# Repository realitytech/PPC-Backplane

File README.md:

# PPC-Backplane
Amstrad PPC640 and PPC512 Internal PC104 Backplane

This adds an internal PC104 compatible slot to the PPC640 and PPC512 in the modem bay.
The board is designed to fit inside the machine soldering on the underside of the main board but can be fitted with through hole sockets and used externally too for testing and development.

This is the inital release version and corrects a few issues with the very first issue. The schematic and PCB need tidying.

NOTE: This version is UNTESTED and has not been built yet. It *should* work as it's an evolution of a design that DOES work. However it's missing changes that the test board has, notably.
Pullups on A8-A16, these seem to be not needed on all units.
Pullups on D0-D7 are optional, both units I have here already have these on the board.

The plan is to move to 74xxx16245 chips to keep to two chips but buffer ALL lines.

Licence/Useage:
Please credit the source. This is a non-commercial project and you may do with it as you wish for PERSONAL USE ONLY
Commercial use is strictly forbidden.

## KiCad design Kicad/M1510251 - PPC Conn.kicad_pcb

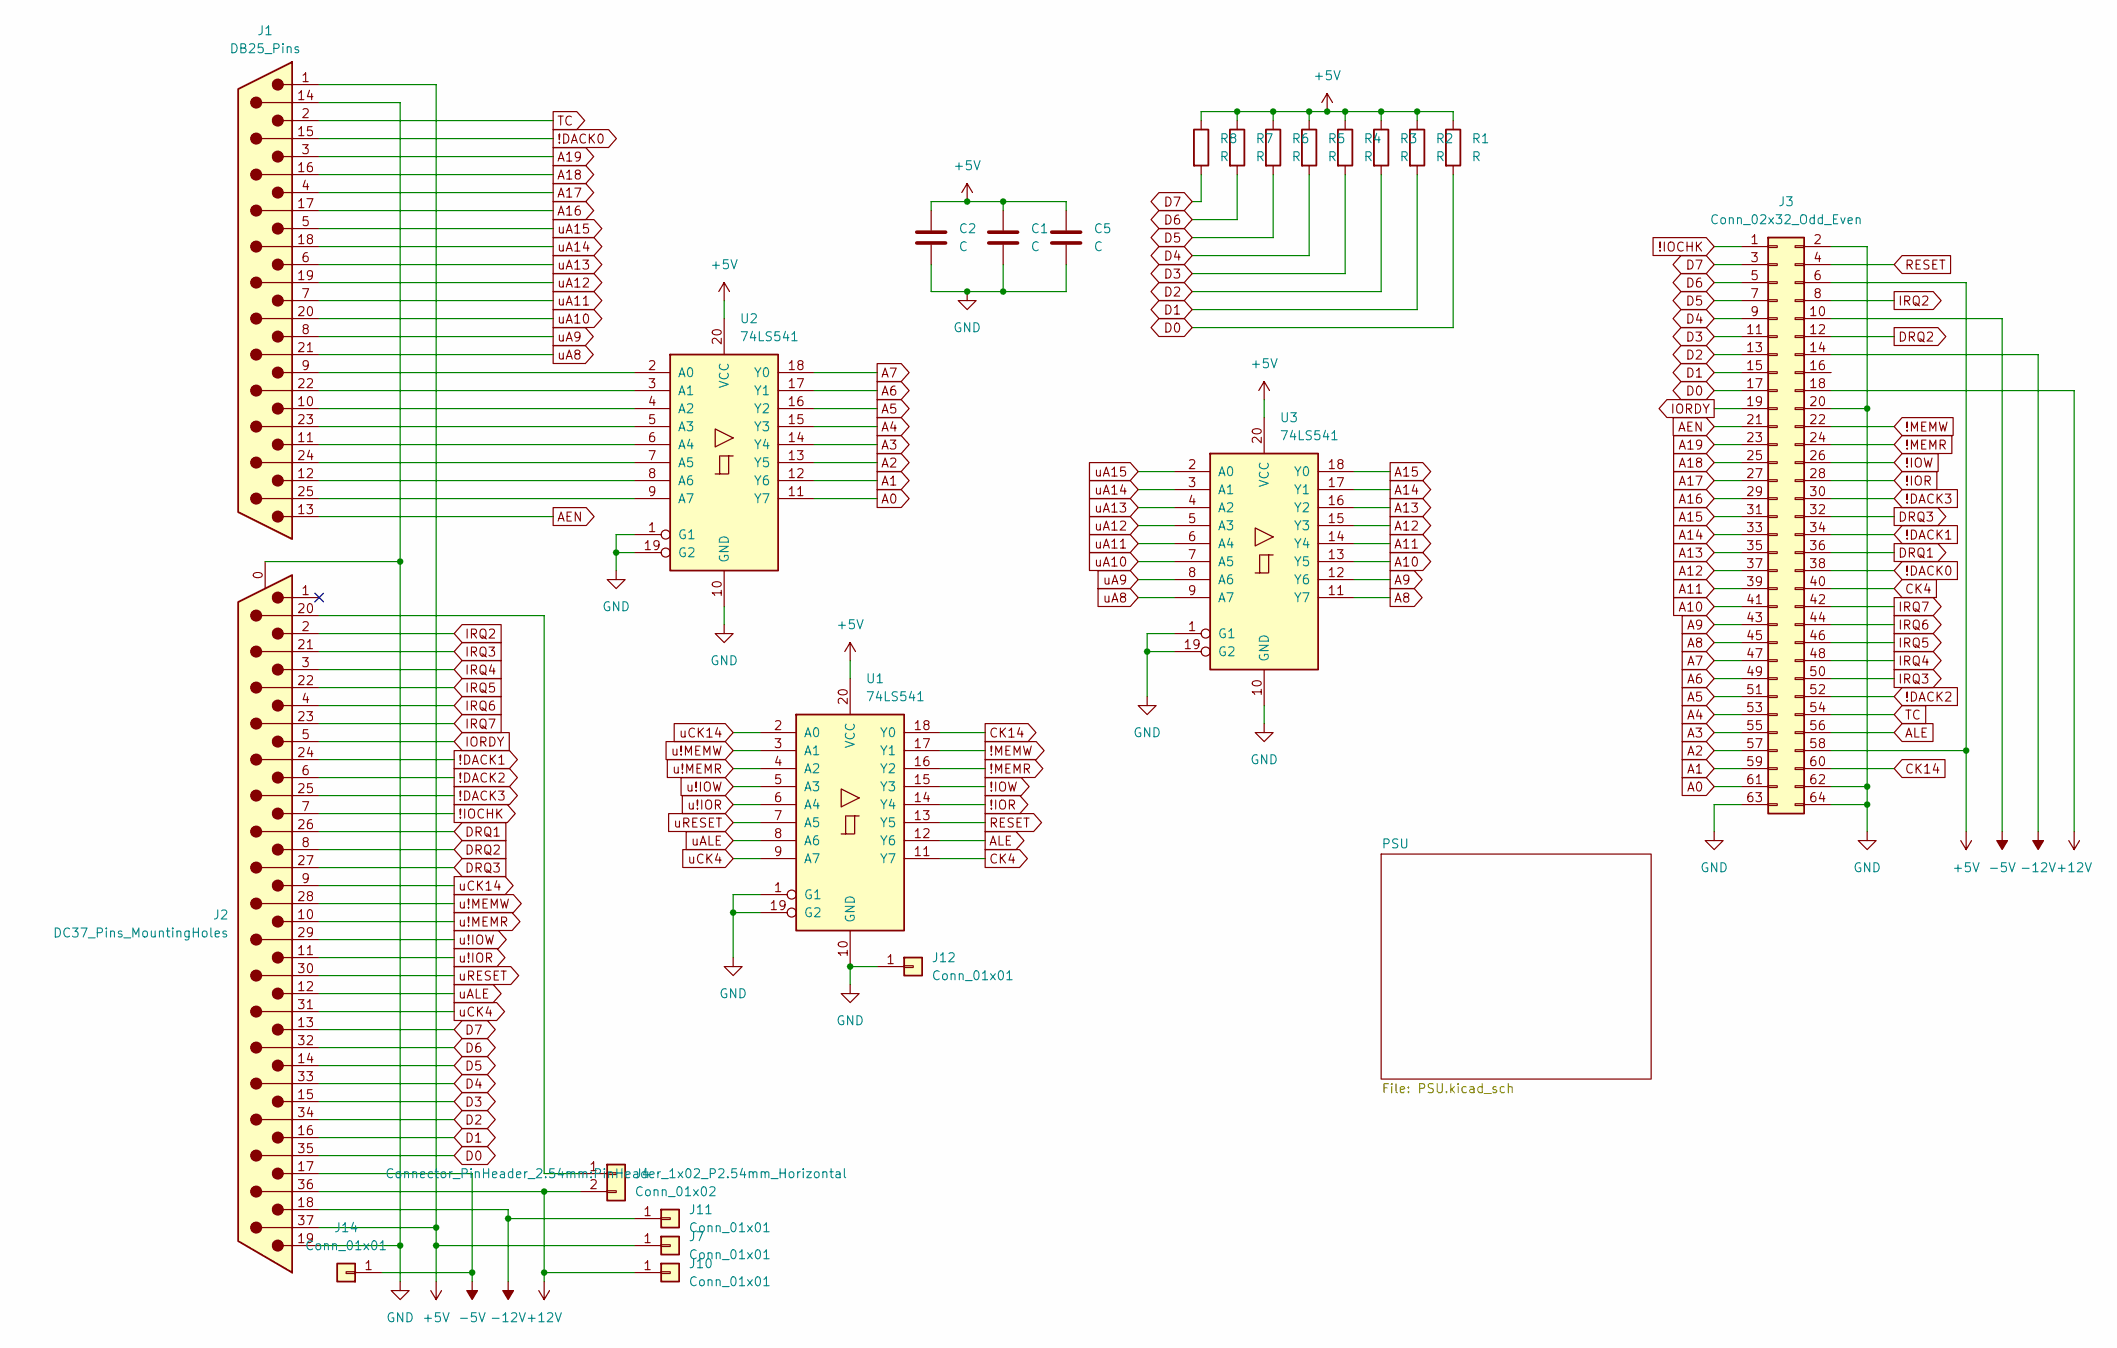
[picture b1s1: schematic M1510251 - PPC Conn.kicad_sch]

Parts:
C1, C2, C5: C; C_0805_2012Metric
J1: DB25_Pins; DSUB-25_Pins_Vertical_P2.77x2.84mm_MountingHoles
J2: DC37_Pins_MountingHoles; DSUB-37_Pins_Vertical_P2.77x2.84mm_MountingHoles
J3: Conn_02x32_Odd_Even; PinHeader_2x32_P2.54mm_Vertical
J4: Conn_01x02; PinHeader_1x02_P2.54mm_Horizontal
J7, J10, J11, J12, J14: Conn_01x01; SolderWire-0.15sqmm_1x01_D0.5mm_OD1.5mm
R1, R2, R3, R4, R5, R6, R7, R8: R; R_0805_2012Metric
U1, U2, U3: 74LS541; SSOP-20_4.4x6.5mm_P0.65mm

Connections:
!DACK0: J1.15, J3.38
!DACK1: J2.24, J3.34
!DACK2: J2.6, J3.52
!DACK3: J2.25, J3.30
!IOCHK: J2.7, J3.1
!IOR: J3.28, U1.14 (Y4)
!IOW: J3.26, U1.15 (Y3)
!MEMR: J3.24, U1.16 (Y2)
!MEMW: J3.22, U1.17 (Y1)
+5V: C1.1, C2.1, C5.1, J1.1, J2.37, J3.6, J3.58, J7.1, R1.1, R2.1, R3.1, R4.1, R5.1, R6.1, R7.1, R8.1, U1.20 (VCC), U2.20 (VCC), U3.20 (VCC); also elsewhere on the board
+12V: J2.36, J3.18, J4.2, J10.1; also elsewhere on the board
-5V: J2.17, J3.10, J14.1; also elsewhere on the board
-12V: J2.18, J3.14, J11.1; also elsewhere on the board
A0: J3.61, U2.11 (Y7)
A1: J3.59, U2.12 (Y6)
A2: J3.57, U2.13 (Y5)
A3: J3.55, U2.14 (Y4)
A4: J3.53, U2.15 (Y3)
A5: J3.51, U2.16 (Y2)
A6: J3.49, U2.17 (Y1)
A7: J3.47, U2.18 (Y0)
A8: J3.45, U3.11 (Y7)
A9: J3.43, U3.12 (Y6)
A10: J3.41, U3.13 (Y5)
A11: J3.39, U3.14 (Y4)
A12: J3.37, U3.15 (Y3)
A13: J3.35, U3.16 (Y2)
A14: J3.33, U3.17 (Y1)
A15: J3.31, U3.18 (Y0)
A16: J1.17, J3.29
A17: J1.4, J3.27
A18: J1.16, J3.25
A19: J1.3, J3.23
AEN: J1.13, J3.21
ALE: J3.56, U1.12 (Y6)
CK4: J3.40, U1.11 (Y7)
CK14: J3.60, U1.18 (Y0)
D0: J2.35, J3.17, R1.2
D1: J2.16, J3.15, R2.2
D2: J2.34, J3.13, R3.2
D3: J2.15, J3.11, R4.2
D4: J2.33, J3.9, R5.2
D5: J2.14, J3.7, R6.2
D6: J2.32, J3.5, R7.2
D7: J2.13, J3.3, R8.2
DRQ1: J2.26, J3.36
DRQ2: J2.8, J3.12
DRQ3: J2.27, J3.32
GND: C1.2, C2.2, C5.2, J1.14, J2.0 (PAD), J2.19, J3.2, J3.20, J3.62, J3.63, J3.64, J12.1, U1.1 (G1), U1.10 (GND), U1.19 (G2), U2.1 (G1), U2.10 (GND), U2.19 (G2), U3.1 (G1), U3.10 (GND), U3.19 (G2); also elsewhere on the board
IORDY: J2.5, J3.19
IRQ2: J2.2, J3.8
IRQ3: J2.21, J3.50
IRQ4: J2.3, J3.48
IRQ5: J2.22, J3.46
IRQ6: J2.4, J3.44
IRQ7: J2.23, J3.42
unnamed: J1.22, U2.3 (A1)
unnamed: J1.23, U2.5 (A3)
unnamed: J1.24, U2.7 (A5)
unnamed: J1.25, U2.9 (A7)
unnamed: J2.20, J4.1
unnamed: J1.9, U2.2 (A0)
unnamed: J1.10, U2.4 (A2)
unnamed: J1.11, U2.6 (A4)
unnamed: J1.12, U2.8 (A6)
RESET: J3.4, U1.13 (Y5)
TC: J1.2, J3.54
u!IOR: J2.11, U1.6 (A4)
u!IOW: J2.29, U1.5 (A3)
u!MEMR: J2.10, U1.4 (A2)
u!MEMW: J2.28, U1.3 (A1)
uA8: J1.21, U3.9 (A7)
uA9: J1.8, U3.8 (A6)
uA10: J1.20, U3.7 (A5)
uA11: J1.7, U3.6 (A4)
uA12: J1.19, U3.5 (A3)
uA13: J1.6, U3.4 (A2)
uA14: J1.18, U3.3 (A1)
uA15: J1.5, U3.2 (A0)
uALE: J2.12, U1.8 (A6)
uCK4: J2.31, U1.9 (A7)
uCK14: J2.9, U1.2 (A0)
uRESET: J2.30, U1.7 (A5)

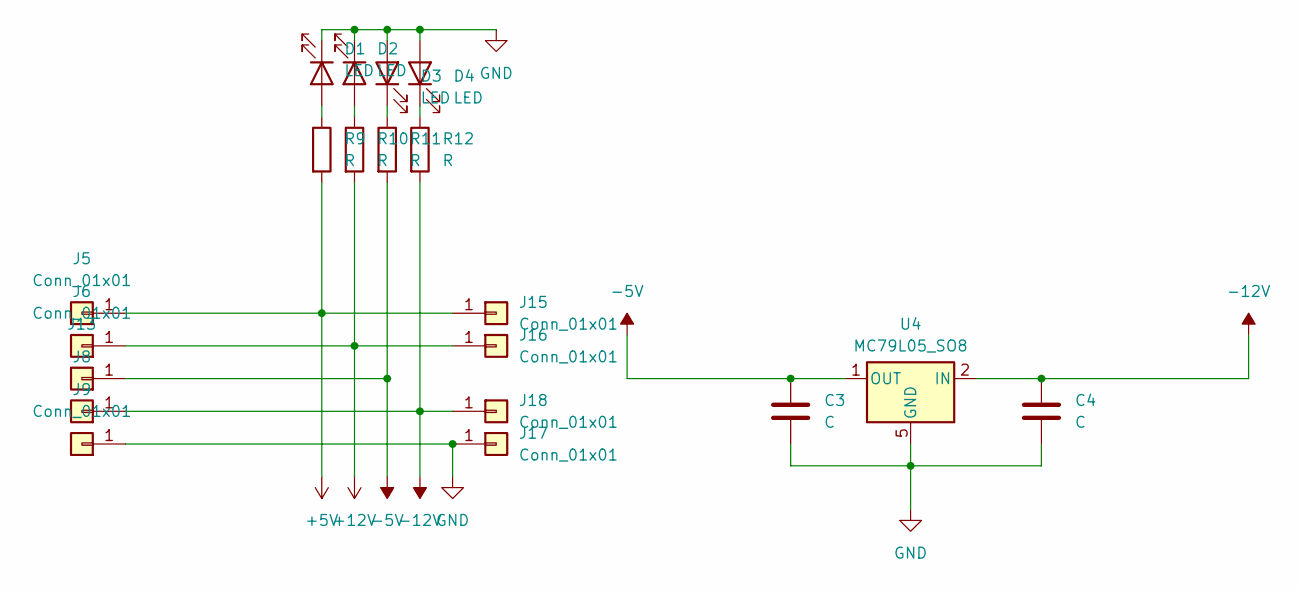
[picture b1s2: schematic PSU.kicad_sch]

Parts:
C3, C4: C; C_0805_2012Metric
D1, D2, D3, D4: LED; LED_0805_2012Metric
J5, J6, J8, J9, J13, J15, J16, J17, J18: Conn_01x01; SolderWire-0.15sqmm_1x01_D0.5mm_OD1.5mm
R9, R10, R11, R12: R; R_0805_2012Metric
U4: MC79L05_SO8; SOIC-8_3.9x4.9mm_P1.27mm

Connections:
+5V: J5.1, J15.1, R9.2; also elsewhere on the board
+12V: J6.1, J16.1, R10.2; also elsewhere on the board
-5V: C3.1, J13.1, R11.2, U4.1 (OUT); also elsewhere on the board
-12V: C4.1, J8.1, J18.1, R12.2, U4.2 (IN), U4.3 (IN), U4.6 (IN), U4.7 (IN); also elsewhere on the board
GND: C3.2, C4.2, D1.1 (K), D2.1 (K), D3.2 (A), D4.2 (A), J9.1, J17.1, U4.5 (GND); also elsewhere on the board
unnamed: D1.2 (A), R9.1
unnamed: D2.2 (A), R10.1
unnamed: D3.1 (K), R11.1
unnamed: D4.1 (K), R12.1

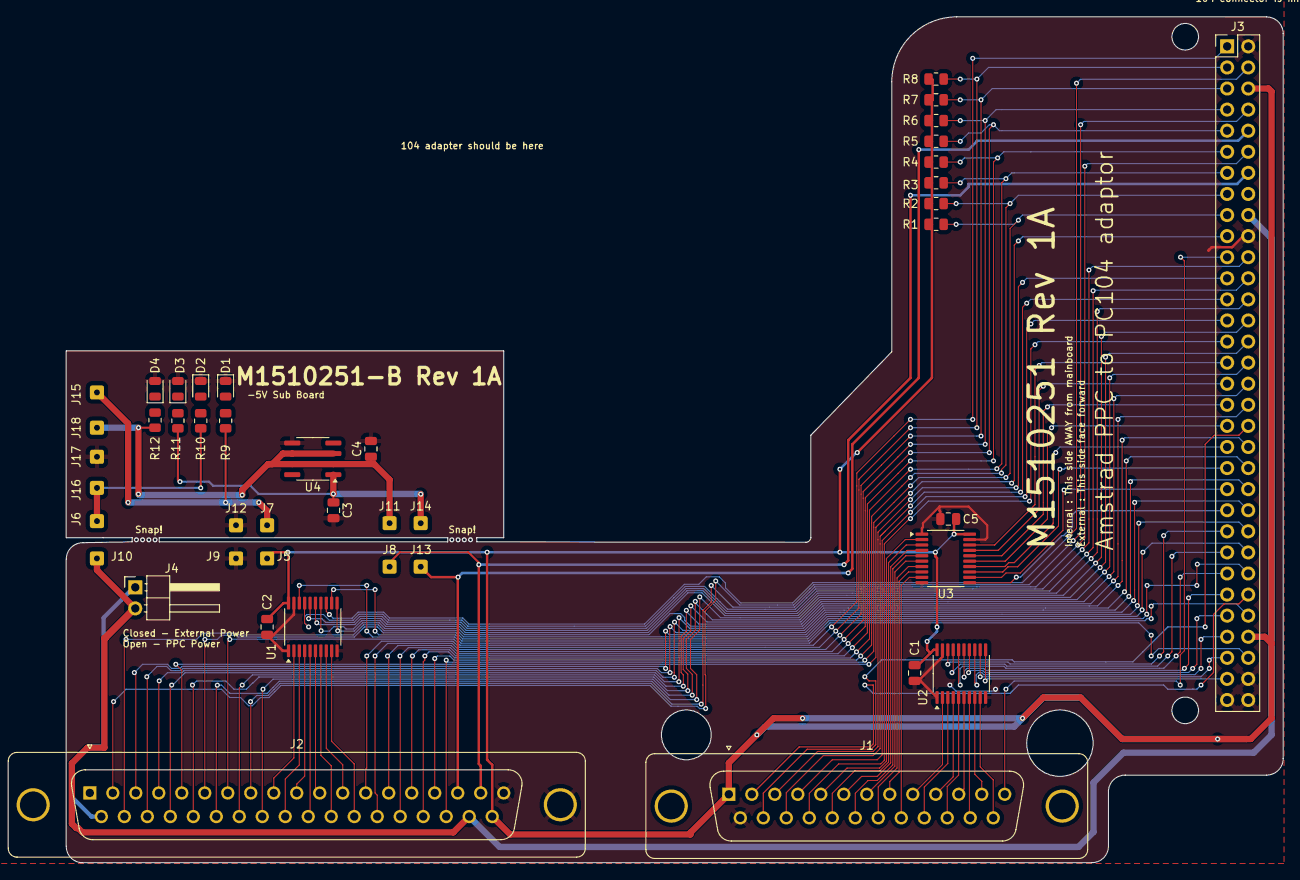
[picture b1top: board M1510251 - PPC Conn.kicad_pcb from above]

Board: 2 copper layers, 146.6 x 101.9 mm, 43 parts (0 on the bottom side), 87 nets.
